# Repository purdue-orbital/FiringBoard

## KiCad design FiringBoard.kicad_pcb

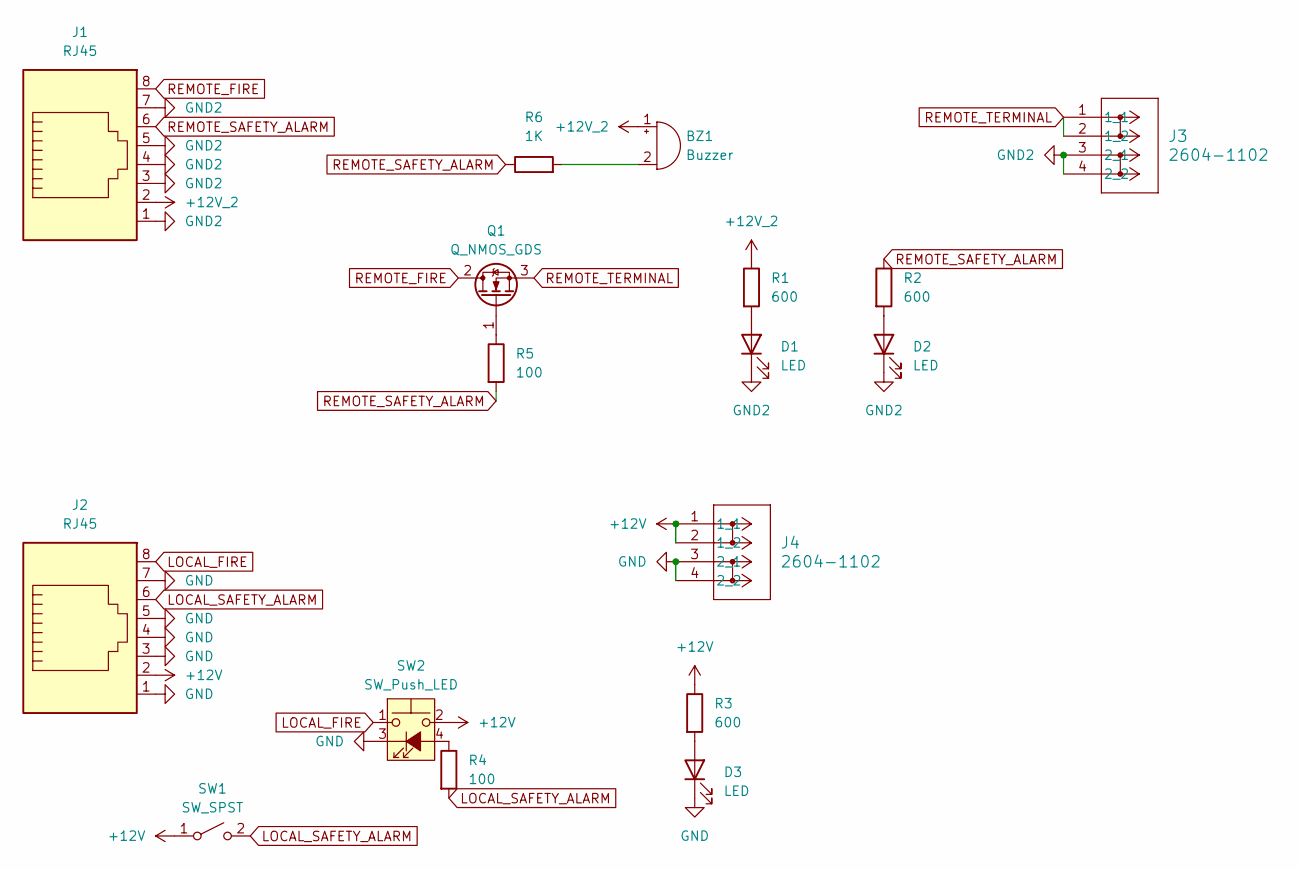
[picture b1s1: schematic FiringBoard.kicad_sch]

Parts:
BZ1: Buzzer; Buzzer_15x7.5RM7.6
D1, D2, D3: LED; LED_D5.0mm
J1, J2: RJ45; CONN8_2-908LF_AMP
J3, J4: 2604-1102; CONN2_2604-1102_WAG
Q1: Q_NMOS_GDS; TO-220-3_Vertical
R1, R2, R3: 600; R_0402_1005Metric
R4, R5: 100; R_0402_1005Metric
R6: 1K; R_0402_1005Metric
SW1: SW_SPST; Switch
SW2: SW_Push_LED; ButtonLED

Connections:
+12V: J2.2, J4.1 (1_1), J4.2 (1_2), R3.1, SW1.1 (A), SW2.2
+12V_2: BZ1.1 (+), J1.2, R1.1
GND: D3.1 (K), J2.1, J2.3, J2.4, J2.5, J2.7, J4.3 (2_1), J4.4 (2_2), SW2.3 (K)
GND2: D1.1 (K), D2.1 (K), J1.1, J1.3, J1.4, J1.5, J1.7, J3.3 (2_1), J3.4 (2_2)
LOCAL_FIRE: J2.8, SW2.1
LOCAL_SAFETY_ALARM: J2.6, R4.2, SW1.2 (B)
unnamed: BZ1.2 (-), R6.2
unnamed: D1.2 (A), R1.2
unnamed: D2.2 (A), R2.2
unnamed: D3.2 (A), R3.2
unnamed: Q1.1 (G), R5.1
unnamed: R4.1, SW2.4 (A)
REMOTE_FIRE: J1.8, Q1.2 (D)
REMOTE_SAFETY_ALARM: J1.6, R2.1, R5.2, R6.1
REMOTE_TERMINAL: J3.1 (1_1), J3.2 (1_2), Q1.3 (S)

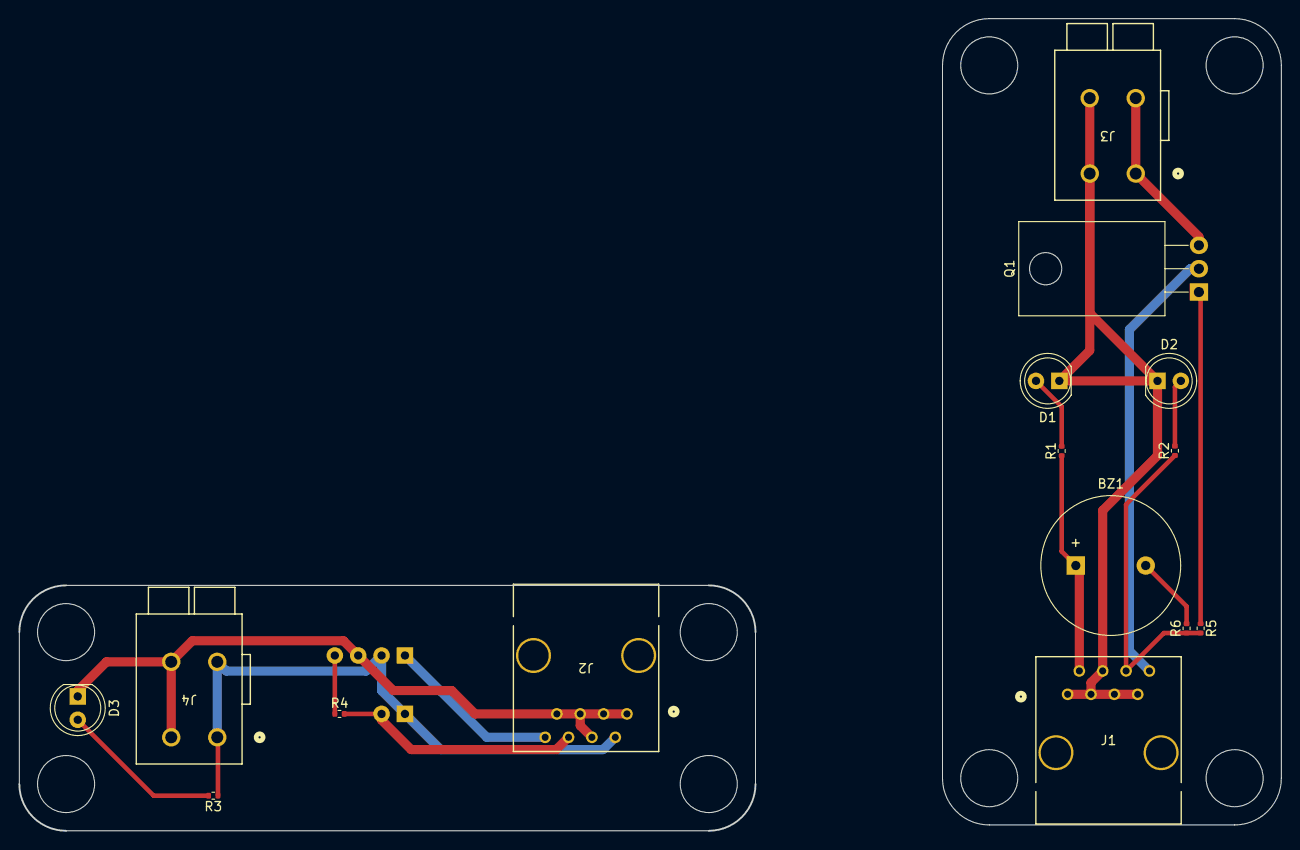
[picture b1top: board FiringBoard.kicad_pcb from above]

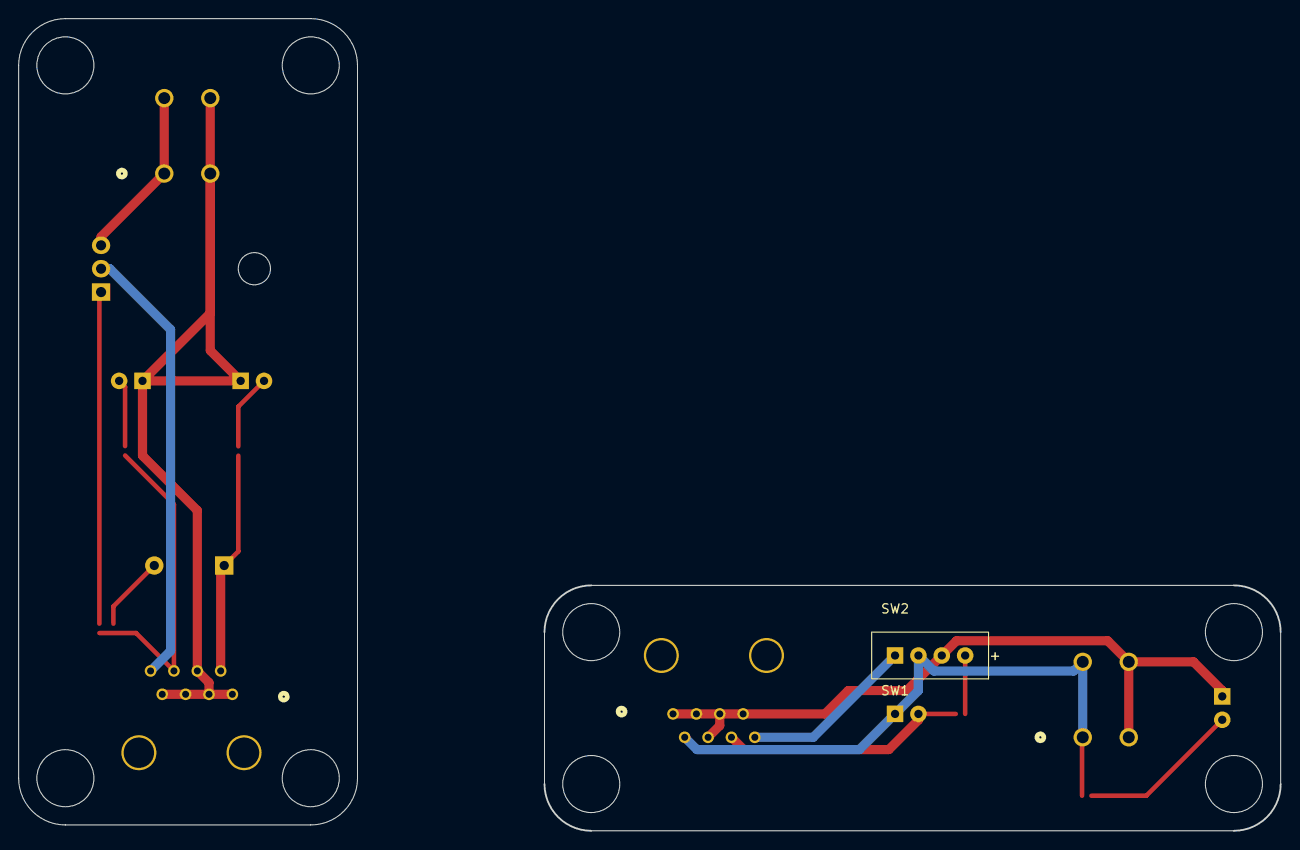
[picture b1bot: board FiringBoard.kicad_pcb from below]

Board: 2 copper layers, 137.2 x 88.3 mm, 17 parts (2 on the bottom side), 15 nets.
